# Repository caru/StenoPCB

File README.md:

Copyright 2014 Emanuele Caruso. See LICENSE for details.

StenoPCB is the PCB design in KiCad for [StenoBoard](http://stenoboard.com) keyboards.

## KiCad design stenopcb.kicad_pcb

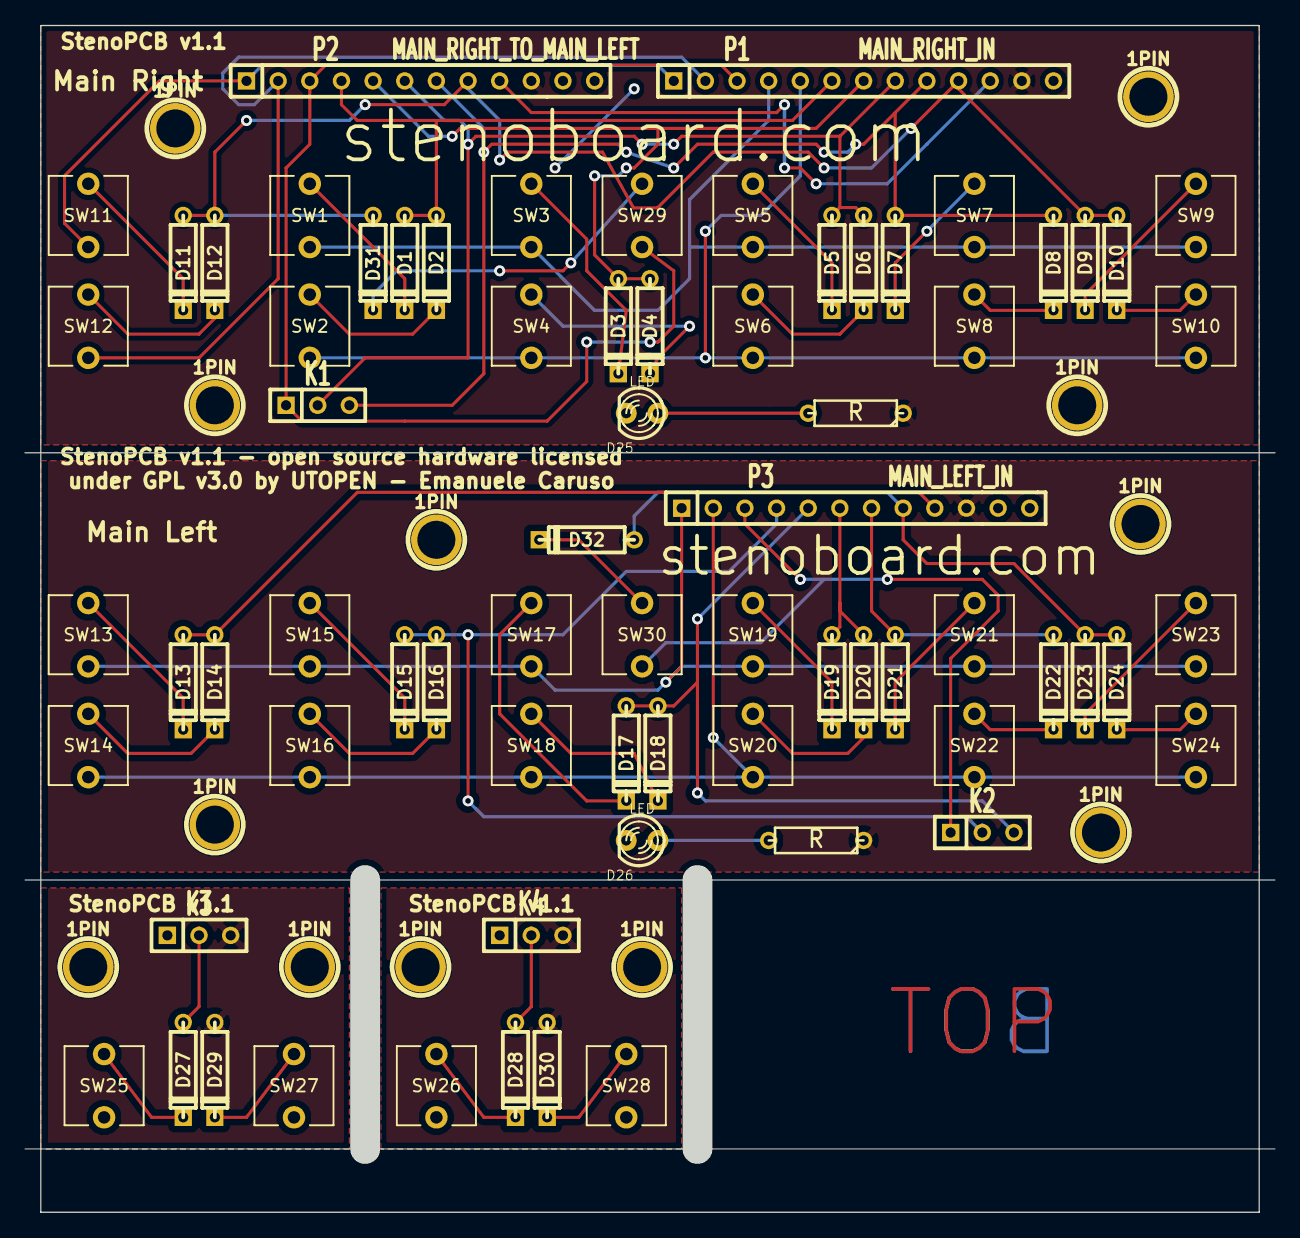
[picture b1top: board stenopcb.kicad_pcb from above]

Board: 2 copper layers, 100.3 x 95.2 mm, 83 parts (0 on the bottom side), 62 nets.

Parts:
1PIN, 1PIN#2, 1PIN#3, 1PIN#4, 1PIN#5, 1PIN#6, 1PIN#7, 1PIN#8, 1PIN#9, 1PIN#10, 1PIN#11, 1PIN#12: P***; 1pin
D1, D2, D3, D4, D5, D6, D7, D8, D9, D10, D11, D12, D13, D14, D15, D16, D17, D18, D19, D20, D21, D22, D23, D24, D27, D28, D29, D30, D31, D32: DIODE; D3
D25, D26: LED; LED-3MM
K1: MAIN_RIGHT_TO_VOWELS_RIGHT; SIL-3
K2: MAIN_LEFT_TO_VOWELS_LEFT; SIL-3
K3: VOWELS_RIGHT_IN; SIL-3
K4: VOWELS_LEFT_IN; SIL-3
P1: MAIN_RIGHT_IN; SIL-13
P2: MAIN_RIGHT_TO_MAIN_LEFT; SIL-12
P3: MAIN_LEFT_IN; SIL-12
R1, R2: R; R3
SW1, SW2, SW3, SW4, SW5, SW6, SW7, SW8, SW9, SW10, SW11, SW12, SW13, SW14, SW15, SW16, SW17, SW18, SW19, SW20, SW21, SW22, SW23, SW24, SW25, SW26, SW27, SW28, SW29, SW30: SPST; EVQ-P0E07K

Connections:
/COL_0: D1.1, D2.1, P1.6, P2.4
/COL_1: D3.1, D4.1, P1.7, P2.5
/COL_2: D5.1, D6.1, K1.2, P1.8, P2.6
/COL_3: D7.1, D8.1, K1.3, P1.9, P2.7
/COL_4: D9.1, D10.1, D11.1, D12.1, D31.1, P1.10, P2.8
/COL_5: P1.11, P2.9
/GND: D25.2, P1.13, P2.11
/LED: P1.12, P2.10, R1.1
/L_COL_0: D15.1, D16.1, K2.2, P3.4
/L_COL_1: D17.1, D18.1, K2.3, P3.5
/L_COL_2: D19.1, D20.1, P3.6
/L_COL_3: D21.1, D22.1, P3.7
/L_COL_4: D23.1, D24.1, D32.1, P3.8
/L_COL_5: D13.1, D14.1, P3.9
/L_GND: D26.2, P3.11
/L_LED: P3.10, R2.1
/L_ROW_0: P3.1, SW13.2, SW15.2, SW17.2, SW19.2, SW21.2, SW23.2
/L_ROW_1: P3.2, SW14.2, SW16.2, SW18.2, SW20.2, SW22.2, SW24.2
/L_ROW_2: K2.1, P3.3, SW30.2
/ROW_0: P1.1, P2.1, SW11.2
/ROW_1: P1.2, P2.2, SW12.2
/ROW_2: K1.1, P1.3, P2.3, SW29.2
/ROW_3: P1.4, SW1.2, SW3.2, SW5.2, SW7.2, SW9.2
/ROW_4: P1.5, SW2.2, SW4.2, SW6.2, SW8.2, SW10.2
/VL_COL_0: D28.1, K4.2
/VL_COL_1: D30.1, K4.3
/VL_ROW_2: K4.1, SW26.2, SW28.2
/VR_COL_2: D27.1, K3.2
/VR_COL_3: D29.1, K3.3
/VR_ROW_2: K3.1, SW25.2, SW27.2
unnamed: D14.2, SW14.1
unnamed: D13.2, SW13.1
unnamed: D24.2, SW24.1
unnamed: D23.2, SW23.1
unnamed: D28.2, SW26.1
unnamed: D30.2, SW28.1
unnamed: D27.2, SW25.1
unnamed: D29.2, SW27.1
unnamed: D32.2, SW30.1
unnamed: D31.2, SW29.1
unnamed: D26.1, R2.2
unnamed: D25.1, R1.2
unnamed: D6.2, SW6.1
unnamed: D8.2, SW8.1
unnamed: D7.2, SW7.1
unnamed: D5.2, SW5.1
unnamed: D11.2, SW11.1
unnamed: D10.2, SW10.1
unnamed: D12.2, SW12.1
unnamed: D9.2, SW9.1
unnamed: D1.2, SW1.1
unnamed: D2.2, SW2.1
unnamed: D4.2, SW4.1
unnamed: D3.2, SW3.1
unnamed: D19.2, SW19.1
unnamed: D21.2, SW21.1
unnamed: D20.2, SW20.1
unnamed: D22.2, SW22.1
unnamed: D15.2, SW15.1
unnamed: D18.2, SW18.1
unnamed: D16.2, SW16.1
unnamed: D17.2, SW17.1

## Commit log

2014-05-06 updated gitignore
2014-05-08 changed output directory
2014-05-11 Added readme and license
2014-05-11 added autosaved files to .gitignore
2014-06-27 fixed 3-pin connector on main right, and made vowel boards smaller
2014-06-27 added information text on silkscreen
2014-06-27 added TOP and BOT copper layers labels
2014-06-27 added bottom margin
2014-06-30 fix silkscreen issues and user text tweaks
2014-06-30 fixed minor silkscreen text issue
2014-07-27 v1.1

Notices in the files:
stenopcb.kicad_pcb:
StenoPCB v1.1 - open source hardware licensed
under GPL v3.0 by UTOPEN - Emanuele Caruso
